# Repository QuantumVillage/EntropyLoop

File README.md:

```
   _   _   _   _   _   _   _  
  / \ / \ / \ / \ / \ / \ / \ 
 ( E | N | T | R | O | P | Y )
  \_/ \_/_\_/_\_/_\_/_\_/ \_/ 
        / \ / \ / \ / \       
       ( L | O | O | P )      
        \_/ \_/ \_/ \_/                                                                                                         
```

**An open source Phase-Diffusion Quantum Random Number Generator**

**2026-04-17 UPDATE** - Now the first AI native QRNG! [/mcp](/mcp) and away!

QV is pleased to be releasing the ‘Entropy Loop’ for world Quantum Day on April 14th 2026: This is a USD $35 open source Quantum Random Number Generator made using off the shelf fiber optics and a raspberry pi pico - in a credit-card sized package!!

Entropy is fast becoming a fundamental resource, especially as AI, simulations, optimizers, cryptography, and computing in general are all changing and accelerating in reach and usefulness. We believe the best way to democratize this technology is to open source a ‘strong minimal viable example’, as we did with quantum sensing, and provide a fully working off the shelf BOM with firmware that passes all major entropy quality tests. This project also serves as an educational/informational demonstration of the benefits of Quantum RNG over regular TRNG and (CS)PRNG technologies.

**Coming Soon** - We want to illustrate a few key use cases for quantum entropy; AI, Simulations, and ART!

Here's what the completed build looks like:

## Randomness from Vacuum Fluctuations

When a laser diode powers up, there are quantum fluctuations that occur that later determine the laser's current phase and polarization during operation. This means that if we pulse a laser diode on, then off long enough to let it totally power down, and then repeat, each pulse has unique and 'quantum random'-ly determined properties. 

We can send these pulses into an optical fiber network, and split the pulse so that ~50% goes straight over to the detector, and the rest gets sent to a delay line - here, we use 5m length of fiber as our photonic delay line. 5m is long enough that with the timing of our pulses (roughly every 24ns, @ 42MHz) the pulse travelling over the delay loop will interact with the next pulse from the laser diode. 

The fact that each of these have different phase and polarization properties, and randomly so, means that their interactions are fundamentally chaotic and random. This is great, for a QRNG - and so this is what we estimate and measure. You can see examples of the pulses below. 

Details for the background physics maybe found in the paper [Ultra-fast quantum randomness generation by accelerated phase diffusion in a pulsed laser diode](https://opg.optica.org/oe/fulltext.cfm?uri=oe-22-2-1645) by Abellán et al.

## Build Instructions

If you would like to jump to our build guide for the Entropy Loop, take a look at [BUILD.md](BUILD.md). 

## System Overview

Here's an overview flowchart of what's going on in this system:

```mermaid
---
title: PD-QRNG Process Flow
---

flowchart TD
    subgraph Fiber Optics
    L[Laser Diode]
    D[Detector]
    end
    subgraph R[<div style="width:30em; height:8em; display:flex; justify-content: flex-start;">Raspberry Pi Pico</div>]
        I[Pi Pico Init]
        subgraph PIO [<div style="width:10em; height:8em; display:flex; justify-content: flex-start;">PIO</div>]
        A[Narrow Pulse Wave]
        end
        subgraph Core 1
        G[Gather Entropy]
        end
        subgraph Core 2
        M[Calculate Min-Entropy]
        S[Generate SHA512 Hashes]
        U[Send Data over UART]
        end
    end
    B[USB Bridge]
    I -->|Initializes Cores| G[Gather Entropy]
    I -->|Loads PIO Program| A
    D -->|ADC read| G
    G -->|Process Data| M
    G -->|Load Raw Samples| S
    S --> U
    M --> U
    U -->|Go Back for More| G
    A  -->|Drives| L
    L e1@==>|pulses sent through fiber network| D
    e1@{ animate: true }
    U ==>|Serial Connection| B
```

### Software Overview

The software is available in C and MicroPython. This guide covers the C code, but there is a commented variant in MicroPython located in [python-scripts/QRNG.py](python-scripts/QRNG.py). The only difference is that MicroPython doesn't have SHA512 available, so we use SHA256 instead. 

There are three parts to this system; the PIO program, the ADC acquisition code, and the min-entropy calculation and hashing code communicating over UART over USB.

The Pi Pico is overclocked to 244.8MHz to synchronize the laser pulse cycle with the propagation delay of light through a 5-meter fiber optic cable.

The timing is based on the speed of light in the fiber, calculated using its refractive index. (For Corning SMF-28 fiber, the refractive index is approximately 1.4682 at 1550 nm and 1.4676 at 1310 nm.) This results in a propagation delay of approximately 24.49 ns over 5 meters at either wavelength.

The PIO pulse cycle consists of six clock cycles: one cycle with the laser on, followed by five cycles with the laser off to allow the laser diode to fully desaturate before the next pulse. Matching this six-cycle period to the fiber propagation delay produces an ideal system clock frequency of approximately 245 MHz.

The Pico is therefore configured to operate at 244.8 MHz, the nearest achievable clock frequency to the calculated optimum. At this frequency, each clock cycle lasts approximately 4.085 ns, producing a laser-on pulse of 4.085 ns followed by a laser-off interval of 20.425 ns. The complete pulse cycle is 24.51 ns, closely matching the fiber's optical propagation delay of 24.49 ns.

This timing is intended to ensure that the laser diode has sufficient time to desaturate between pulses, allowing vacuum fluctuations to contribute to the randomness of the emitted photons while maintaining synchronization with the optical delay line.

The PIO code sets is as follows:

```c
.wrap_target
    set pins, 1 
    set pins, 0 [4]
.wrap
```

The code on core 0 is the ADC acquisition code. It reads the signal that is biased at 1.65V, exactly in the center of the Pico's 3.3V ADC range. The ADC is 12-bit, meaning our readings are centered around the value 2048, with a maximum of 4096. The ADC measurements are collected in window arrays of length 1024 `int` values, and passed through a blocking write to an array owned by core 1. 

Core 1 runs the min-entropy calculation code and manages UART communications. It performs an optimized min-entropy calculation that performs a lagged look-around analysis to generate a histogram of delta difference values for each of the measurements. This normalizes the calculation from being 'peak heavy' from the pulsed nature of the randomness, and attempts to avoid any incidental features from the 500kHz max speed of the Pico's ADC. Given we are using a window of 1024 (2^10) samples, the maximum value for min-entropy is 10. The min-entropy calculation code is as follows:

```c
for(int i = 0; i < BATCH_SIZE; i++) {
    // Mask to ensure we only look at 12 bits
    uint16_t val = batch.samples[i] & 0xFFF;
    
    // --- Update Min/Max (Raw Data) ---
    if (val < min_val) min_val = val;
    if (val > max_val) max_val = val;
    // ---------------------------

    // --- LAGGED DERIVATIVE CALCULATION ---
    // 1. Get the "Old" value from history
    uint16_t old_val = history[hist_head];
    
    // 2. Overwrite history with current value
    history[hist_head] = val;
    
    // 3. Advance the ring buffer head
    hist_head = (hist_head + 1) % LAG_DEPTH;

    // 4. Calculate Delta against the OLD value
    // We add 2048 to center the result.
    uint16_t delta = (val - old_val + 2048) & 0xFFF;
    // -------------------------------------

    // Update Histogram using DELTA
    if(counts[delta] < 65535) counts[delta]++; 
    if(counts[delta] > max_count) {
        max_count = counts[delta];
    }
}

// Calculate Min-Entropy
float min_entropy = 10.0f - log2f((float)max_count);
// scale for 8-bit min-entropy - for 10.0f it's 8/10.0
min_entropy *= (8.0/10.0);

// Calculate Range
uint16_t dynamic_range = max_val - min_val;
```

## Hardware

### Bill of Materials

**Optics:**

* 2x fiber splitters - 1x2 or 2x2
* 1x Delay line (5 meters)
* Optical connectors

For our assembly, we use SC/APC fiber connectors. These are square with angled ends that minimize reflections at any interfaces. 

**Electronics:**

* 1x Raspberry Pi Pico (or Pico 2)
* 1x Prototype Board
* 1x pair of fiber optic transceivers
* 1x 10nF ceramic capacitor
* 2x 10k Ohm resistors (through hole)
* 1x prototyping board
* Assorted connection wires

Many optical transcievers transmit/receive on 1310/1550nm or tx/rx at 1550/1310nm. (1310nm is in O-band and 1550nm is in C-band in conventional fiber optic parlance). 

### Prototype Board Assembly

The following summarises the pin assignments for the Pico:

* `GPIO0` is used as the laser driver. A PIO program is run to offload this from the CPI.
* `ADC0` is used to read the data from the receiver, running on core 0
* The USB port is used to analyse and generate the final randomness and min-entropy outputs, and is controlled from core 1. 

### Optical Assembly

This is a sketch overview of the RPi pico driver, laser/PD and splitter setup. The Delay Loop used below is 5m in length.

This is what the system looks like in hardware:

### Circuit Details

`GPIO0` and `ADC0` are used on the RPi Pico. Here are more details:

* The `3V3` and `GND` pins (3rd and 5th on RHS) are used to power the two fiber modules.
* Both an A and a B module are used - one transmits at 1310 and receives at 1510, the other at 1510 and receives at 1310.
* Pin 8 on the A module (`TX` positive pin) is used to drive the laser.
* Pin 2 on the B module (`RX` positive pin) is used to receive.
* Between this `RX` pin and the `ADC0` pin, there is a small circuit that normalizes the voltage from being centered around 0V to being centered around 1.65V. This circuit is comprised of:
    * 2x 10k Ohm resistors are used. On is connected to `3V3` and the other to `GND` they form a voltage divider the middle of which is tied to `ADC0`.
    * 1x 10nF ceramic capacitor is used - this goes from `RX` to `ADC0` that has the voltage lift from the divider. 

The circuit schematic for the output level shifter looks like this: 

## Bill of Materials

The full BOM is as follows:

1. 1x PAIR Fiber Transcievers - e.g. https://www.aliexpress.com/item/1005010400110455.html
1. 1x 5m fiber patch cable - e.g. https://www.aliexpress.com/item/1005008760544957.html
1. 2x 1x2 50/50 fiber splitters - e.g. https://www.aliexpress.com/item/1005006647801937.html 
1. 3x SC/APC Fiber Couplers - e.g. https://www.aliexpress.com/item/1005008790973325.html
1. 1x Raspberry Pi Pico
1. 1x Prototyping board
1. 2x 10k Ohm Resistors
1. 1x 10nF ceramic capacitor

### Note on Fiber Choices

For our build, we use SC/APC fiber connector parts - these are usually green in colour. SC Connectors are very easy to use and reconfigure, hence they were chosen. Blue SC connectors are UPC, meaning they have flat ends which can cause reflections of signal. SC/APC connectors have an 8 degree angle cut on the end to minimize reflections, which is ideal for our purposes. Yellow fiber cabling is usually patch fiber, which is what we want to use. We use multimode 9/125 fiber in this build - that is 125um diameter with a 9um core. 

The transcievers we use are usually multimode - that is they have one side that transmits on 1310nm and receives on 1510nm frequencies, and the other side receives on 1310nm and transmits on 1510nm light frequencies. We use 1310nm for Tx/Rx, but the choice of which frequency to use is inconsequential.

## Full Build

### Transiever Pinout

The pinout for each transceiver unit is as follows. Pin 1 is the left-most pin when looking down on the top of the device with the fiber pointing away from you. The pinout is as follows:

We will just use the `RD+` and `TD+` pins for Rx/Tx respectively. Note that you have to supply +3.3V to EITHER the `VCCR` on the Rx side and `VCCT` on the Tx side, as they have separate power supplies.

### Build Overview

If you are using the PCB design, you should end up with something that resembles these examples (credit-card for size):

The Pi Pico uses `ADC0` for Rx and `GPIO0` for Tx - with the 3.3V supply and GND pins powering the units. The overall wiring looks like this from below:

Here is the top view - you can see how the voltage divider and ceramic capacitor:

The capacitor is tied to one side on pin 2 of the receive module, and the other side is tied to the joint between the two resistors in the voltage divider. The push pull of the Rx signal is thereby inverted over the capacitor and shifted to 1.65V, which is the precise middle of the 3.3V `ADC0` range. 

### Fiber Build

The fiber is built exactly as photographed above. The setup is symmetrical, so there is no specified in/out or tx/rx port. The two free ports go to either module.

Remember, the fiber network is essentially an amplifier for the quantum vacuum fluctuations in the laser diode startup.

## Results 

The following show some measurement results off a six metre fiber delay loop in a MZI configuration, with a 38MHz base pulse step with 4 sleep steps following. 

This is the base pulse from the PIO program on `GPIO0`:

Here is the base pulse sent over a 1.5m loop of fiber - 

And here is the full output from the `RX` pin sent to the ADC over the interferometry network:

Here are two zoomed in portions to help show the randomness of the system:

<!-- 
 -->

This is a much zoomed in signal from the receiver:

## But How do we Know It's Quantum?

Suppose we take our transciever setup, and run the Pico as normal. Then let's hook it up to the two splitters. If we just connect one of the fibers between the two, we get the following output trace:

However, if we add both fibers, we get the following trace:

The fact that these are so similar is encouraging, as it means that the two signals are either matching, cancelling out, or adding some more noise from the few extra lengths of fiber.

The following is the output when you add the delay line back between one of the connections between the splitters - the dramatic change in the signal despite the same oscilloscope settings means that we are surely seeing some kind of quantum interference resulting from the vacuum fluctuations in the laser diode startup:

We can look at some zoomed-in versions to see the difference. Here is the signal with one connection between the splitters:

Here is the signal zoomed-in with two arms connected - we can see that the signal is in part amplified and in others slightly variable:

With the delay line included, we can see the randomness in the signal from the interference of the non-matching laser pulses:

### Comparison of PIO Signal to Output

Here is the base signal with the base pulse in purple:

Here is the baseline random signal from the interference with the baseline signal in purple again:

Note that there is a 'peak-y-ness' in the signal that correlates with the baseline somewhat. This is why we use jittered readings to avoid falling into traps around that potential correlation. 

## Entropy Tests

### Running `ent`

On a file with 256 million raw bytes converted from the input, the following result was obtained from running the `ent` entropy test suite, a standard tool in Linux:

```bash
user@qrng:~$ ls -l qrng_dump.bin 
-rw-rw-r-- 1 user user 256000000 Feb  4 14:28 qrng_dump.bin
user@qrng:~$ ent -b ./qrng_dump.bin 
Entropy = 1.000000 bits per bit.

Optimum compression would reduce the size
of this 2048000000 bit file by 0 percent.

Chi square distribution for 2048000000 samples is 0.15, and randomly
would exceed this value 69.96 percent of the times.

Arithmetic mean value of data bits is 0.5000 (0.5 = random).
Monte Carlo value for Pi is 3.141611487 (error 0.00 percent).
Serial correlation coefficient is 0.000025 (totally uncorrelated = 0.0).
user@qrng:~$ 
```

Things of note - Entropy of "around 1 bit per bit" is ideal. Chi-squared values need to be between 0.05 and 0.95, so 0.65 is pretty reasonable. Serial correlation less than 0.00005 is usually considered pretty good, too. 

Calculating >2 digits of pi with randomness is pretty hard - this is for the same reason that `22/7` is such an unreasonably good approximation of pi; the continued fraction of pi has a very large term (292) in it's fourth coefficient (`[3;7,15,1,292...]`). This means that getting `3.1416` vs `3.1415...` (0.0001 off) on a reasonably small dataset is encouraging. 

On this test suite, the randomness is performing pretty well, it seems!

### NIST STS

This is a gold-standard test suite from the NIST standardization people. Here is the output of the full run, showing what parameters were used with `sts-2.1.2` version:

```
user@qrng:~/nist/sts-2.1.2/sts-2.1.2$ ./assess 1000000
           G E N E R A T O R    S E L E C T I O N 
           ______________________________________

    [0] Input File                 [1] Linear Congruential
    [2] Quadratic Congruential I   [3] Quadratic Congruential II
    [4] Cubic Congruential         [5] XOR
    [6] Modular Exponentiation     [7] Blum-Blum-Shub
    [8] Micali-Schnorr             [9] G Using SHA-1

   Enter Choice: 0

                User Prescribed Input File: data.bin

                S T A T I S T I C A L   T E S T S
                _________________________________

    [01] Frequency                       [02] Block Frequency
    [03] Cumulative Sums                 [04] Runs
    [05] Longest Run of Ones             [06] Rank
    [07] Discrete Fourier Transform      [08] Nonperiodic Template Matchings
    [09] Overlapping Template Matchings  [10] Universal Statistical
    [11] Approximate Entropy             [12] Random Excursions
    [13] Random Excursions Variant       [14] Serial
    [15] Linear Complexity

         INSTRUCTIONS
            Enter 0 if you DO NOT want to apply all of the
            statistical tests to each sequence and 1 if you DO.

   Enter Choice: 1

        P a r a m e t e r   A d j u s t m e n t s
        -----------------------------------------
    [1] Block Frequency Test - block length(M):         128
    [2] NonOverlapping Template Test - block length(m): 9
    [3] Overlapping Template Test - block length(m):    9
    [4] Approximate Entropy Test - block length(m):     10
    [5] Serial Test - block length(m):                  16
    [6] Linear Complexity Test - block length(M):       500

   Select Test (0 to continue): 0

   How many bitstreams? 200

   Input File Format:
    [0] ASCII - A sequence of ASCII 0's and 1's
    [1] Binary - Each byte in data file contains 8 bits of data

   Select input mode:  1

     Statistical Testing In Progress.........

     Statistical Testing Complete!!!!!!!!!!!!

```

The results are in [`20260209-finalAnalysisReport-nist-sts-2.1.2-1000000-200.txt`](20260209-finalAnalysisReport-nist-sts-2.1.2-1000000-200.txt). Some notes:

* `0.474986 200/200` for Approximate Entropy is a perfect score
* The Universal test (compressibility) has a very fine score at `0.930026 197/200`
* Generally, results are >= 193/200.
* `Frequency: 197/200` is a strong result.
* `Runs: 200/200` (The "Coin Flip" consistency is perfect)
* `FFT: 198/200` (No periodic sine-wave noise detected)
* `Linear Complexity: 199/200` (Mathematically complex)

This is a pretty reliable showing in the NIST STS tests!

## Sample Serial Output

Here is some example output from the UART connection. `H_min` is the output of the min-entropy calculation. When scaled to 8 bits, ~6-6.4 is considered generally good. `R` is the range, and `Data` precedes two lines of `SHA512` hashes that are the condensed versions of the input entropy pools:

```bash
H_min: 6.4000 | R: 1918 | Data: 
443873b9af95c4671de53ede1f37af2f78408a903300402543a34a06020aa305c09b0bcea871f904c372c40d79e6035c89a2711f412869b5a05652051dbfac67
d530286e8019a42a8ae438069d4621a9911630763abc80a3125b4f1f0452eb92756abd615073a2da890c3ca5808bbc866dcea88fa74e5539537c7104e0722f3c
H_min: 6.1425 | R: 1950 | Data: 
f0b5757e5fe9591ffc66a6ced7bf63c96838fa9df56f366fce90f07ed2ef06784f5ba94b515a9a42c2b13a4b6f5175f0dfe105297ab661c1208994a6aca6be4b
33c6c05e40a60159f14c41c28ee8776daf82613df46fb542fcb2eb2bf6d3aae50eab5d88226b226b91baa0837d19b883117379b2ef41808076bb43b0daa5941c
H_min: 6.4000 | R: 2011 | Data: 
2e07d14ec204998db14837cad48da2c273f100264779920bbebb92e8208ab1484c863162b24baa2da8da6b7945f3a7a6f85a936c37de6345f181d7fdb6b4c3a1
26ee2365af42f27a8d64097024393df73e5ea65b2386062645fe1346006324c6d678e08f1b1a32deeb540cefb8a982079c72bc777162d5188ecbac2e398a5b44
H_min: 6.4000 | R: 1986 | Data: 
337e48c7376a80b0e43b932615866200de07d32e855f63956073ab6aa83fb87f9524ecd4503aa5a3633824c69cddad1734a44bc7f0685c7dccec9892455fc66e
4bf61aa3b0e67d1cac27f887e0d6b1aaf26181b14048d6834875f49160590e7c6dd7f5b84c7ef79b4e51ebe840208673d65dd83c78856fea4d1e06def112e8ab
H_min: 5.7541 | R: 1828 | Data: 
cc973979268c01a256b1f7c1f226f3741a06034923c8cb8b452da0b09ffa05b256df2bde82461249158728a9bb74b89143cb34be45561cf723f64201bb5d9547
286caf718f46534027ddc94c3432383939fdc79027dbcb5a487c42e33cb09bf8876675718b4c37cc42f7378736ace144857e9b767dac2c30c2549cc81d4ee1b4
H_min: 6.4000 | R: 1839 | Data: 
6aa747abc770854975d74c763407b2fd151ebbc53ae27084d2d55084dcf394903a6c9841217591ff92a13f3f10bfd8a3b82c2b0ce2ef096590024fd1c93d56fd
62b8e07aaeb52128169e41d9c77f14a0c66dac61ef11325dba470b5d6005668d14b43e5f44c5a4f657f5f51c45488909abd7a0001b8abc3f05fceae6b3832994
H_min: 6.1425 | R: 2034 | Data: 
853e63609444bd463b8acc818e39d7ad5fba318f25a71634dd97edefaa8078b462a20ffce2dfc9081d327e3bda971b9eb139674d1370379de49f712a601b0178
9fffab38b70490f84225ad8d432040bfa0007604d99cc4d89062b60788177c3dbcf663a890ee3b31fb18d553476f54c8de89823c984ea6653326192da4cfd811
H_min: 5.9320 | R: 1824 | Data: 
15d2f45addaecf805045659a7a7764ef39c73e8e403ee7e37e8bb92ab8482846da3ed463b42cdfaec0f1c1c84dd400c69c32312f63d3d16044a192cc7ef23752
8d1ec1bb5ae9b8588219cf4f12aad1076d1c6872df68ea6e431a4a24e1f4c5bf793d33a27da6aa7d012d2c338c6333ad42dd180820311d8c6ef9d81230558f09
H_min: 6.4000 | R: 2021 | Data: 
fa5ad3478acb174873311625d4d543d1edf3c6c6527002d0a374e4af4fe89c67988e25f0669d5a84ef9f2f0f285fa8ef56c92ed165c887603dddd20afca39cba
1028a9831090576b02f8fdb6ef68872d2b4e0f4b1823a0cba7e9f82718e798b06928d22fb90b1668b8a0e0b8a9cfe79cd492e64aee1fd4e48294420a93d37da4
H_min: 6.4000 | R: 1936 | Data: 
ed30f574e2b04bcb051d67047dde8a0842dd2fda9098914daa70570892391264a113f031553a4eacde3053701320495807773bf609f122554db7c898d7e5c6b3
d029184e8afb121cebfea3a4c23f1165839b05e7b171aff8fbbe77be89a0a07863498280a01d85e3eaa854719aa9a111ded448e6d89e154909b8b328a4f8850b
H_min: 6.4000 | R: 1940 | Data: 
2ba336de86fc9a3c979d21a3adb4bd92e0ca8911ee1f676723bf9325a9f496e5bc951808f4c43db71a6292a3bccffb4783992e8d1c775b5b7a5650b4d42fb3d7
736276f7c2264c1bad9cadab5a55cb96eb401da8913b35eeccbab3a4fcd762c0a81f7c00122ec527a8f67e59c565ced42ae1a8ac2a3d37f3153fa966e4f99a61
H_min: 6.4000 | R: 1972 | Data: 
103f16490da66756b70ed2787f4012fd5ba894a9067591155c718e8669afb0e979d83f3ec5d531bf9bdecadfd3897eafca9323384daf4a46f4c190820ddfdc82
8ea2d7bd19b792baa3458a0831d71078efcf4232c2d2933966c761e8d36ce8cadcd4cdfee128014802be5315b7761cf34b05069f30be1ab9c4886a65325e7083
H_min: 6.1425 | R: 1956 | Data: 
498b9d036b77fa9294dea3043eb20998103514f0c8c0bfa7c79cc1ee6bee675da76e10db003e2d8d656bafc5954bc816451b48df74ba32cadd5b3161c60cd215
8956642194ae2d9ceaa2e97f69fea594d1ea65ea16b6121be89f465594add880c5d4afc87643768840da0e54124cb81b4bb5abd286c55ef8176980bc72224412
H_min: 6.1425 | R: 1925 | Data: 
07085ec0352fb6853b2a79e40ebb86f2a13166b173c6c21c2f8da378dd93bd50d3d5b95f3514ccfd1517593f589a2fcd1b470937eaaf9a692dff998121a6456a
491454d92d2dcb301fe41e5745cf9fe742fe1e5b04bce5ad51d0d7c6f4eaf318c6ce491ffb21543f7167fc488a2e0523e6a69a21b0c42eca6275b880ce7170a6
H_min: 6.4000 | R: 1954 | Data: 
f0224d88000652e386231a7e596df556c80bb06b99a23a6644ba36cfa9689c4788fcbe78fd053da6b8580fc26c381dd2c3380f86a2839ecde010fbc1ce8810a5
cf9b05b8deddf0c9909b8caf2f479a612f97e9e6e00c2bdc3195e37dc35da1268cd67c73795485f954209cd02709e398533f4efcf8ea30ed7d8ae34f037312d6
H_min: 6.4000 | R: 1855 | Data: 
75fa43d80123b479414758c09433c51612fa482737b2a10c9eee5a64af7895b71b37e265aeb47a38fa77667c40eef1aa162d997e1f256e30ff26280764c04058
567d2cf0192a0301d4f5782d4b8d0cea3e31f43d5b484bd7a4c9850927fadce7082137b5b1346d1c4328f5d6d2528a0421703831c497564db39ba6056ab8fa65
```

## Conclusion

This project has showed the potential for low cost, high performance, field-ready designs for PD-QRNG.

## Acknowledgements 

We are grateful to Eric Case and Dr. Evan Anderson for their help and contributions to validation and testing the design, as well as the Quantum Village community's continued enthusiasm for lo-fi DIY 'bits box' Quantum!

This project was supported by a grant from the Mozilla Foundation to whom we are very grateful.

## References

The primary reference is Abellán et al. "Ultrafast Quantum Randomness Generation by Accelerated Phase Diffusion in a pulsed laser diode", 2014, link: https://opg.optica.org/oe/fulltext.cfm?uri=oe-22-2-1645.

A secondary reference, "Quantum Entropy Source on an InP Photonic Integrated Circuit for Random Number Generation" by Abellán et al. is good resource for understanding vacuum fluctuations, and how they can be utilized; Link: https://opg.optica.org/optica/fulltext.cfm?uri=optica-3-9-989.

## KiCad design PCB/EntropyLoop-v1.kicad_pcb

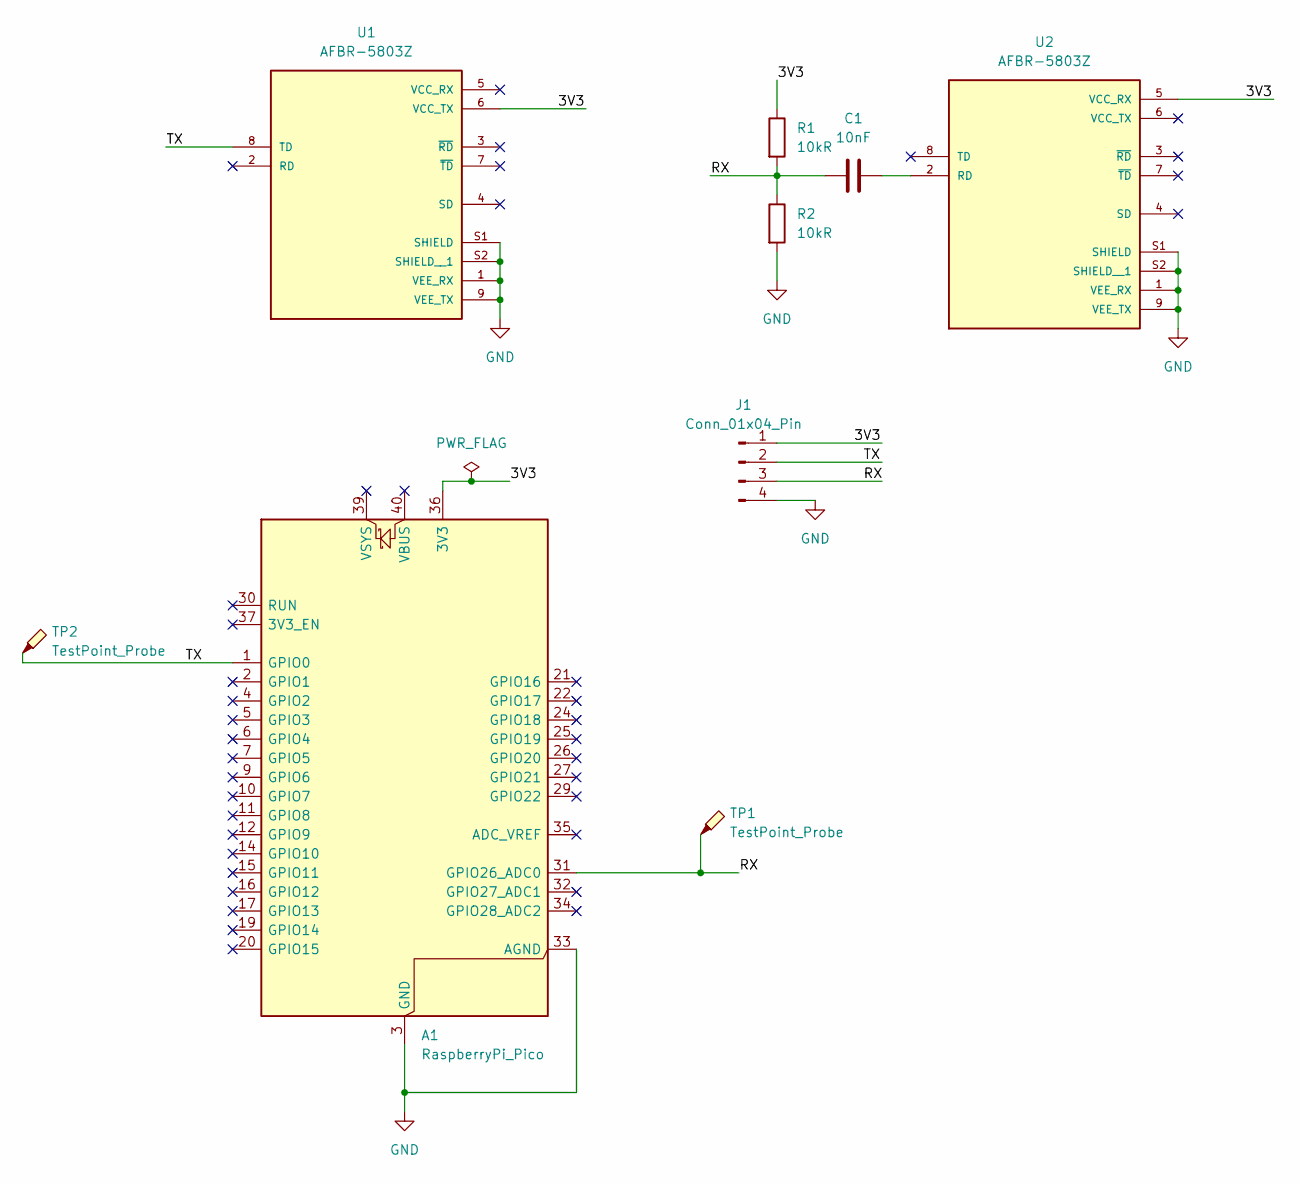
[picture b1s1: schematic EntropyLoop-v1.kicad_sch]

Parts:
A1: RaspberryPi_Pico; RaspberryPi_Pico_Common_Unspecified
C1: 10nF; C_Disc_D4.7mm_W2.5mm_P5.00mm
J1: Conn_01x04_Pin; PinHeader_1x04_P2.54mm_Vertical
R1, R2: 10kR; R_Axial_DIN0207_L6.3mm_D2.5mm_P7.62mm_Horizontal
TP1, TP2: TestPoint_Probe; TestPoint_Loop_D2.54mm_Drill1.5mm_Beaded
U1, U2: AFBR-5803Z; XCVR_AFBR-5803Z; PARTREV March 24, 2017

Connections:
/3V3: A1.36 (3V3), J1.1, R1.1, U1.6 (VCC_TX), U2.5 (VCC_RX)
/RX: A1.31 (GPIO26_ADC0), C1.1, J1.3, R1.2, R2.1, TP1.1
/TX: A1.1 (GPIO0), J1.2, TP2.1, U1.8 (TD)
GND: A1.3 (GND), A1.8 (GND), A1.13 (GND), A1.18 (GND), A1.23 (GND), A1.28 (GND), A1.33 (AGND), A1.38 (GND), J1.4, R2.2, U1.1 (VEE_RX), U1.9 (VEE_TX), U1.S1 (SHIELD), U1.S2 (SHIELD__1), U2.1 (VEE_RX), U2.9 (VEE_TX), U2.S1 (SHIELD), U2.S2 (SHIELD__1)
unnamed: C1.2, U2.2 (RD)

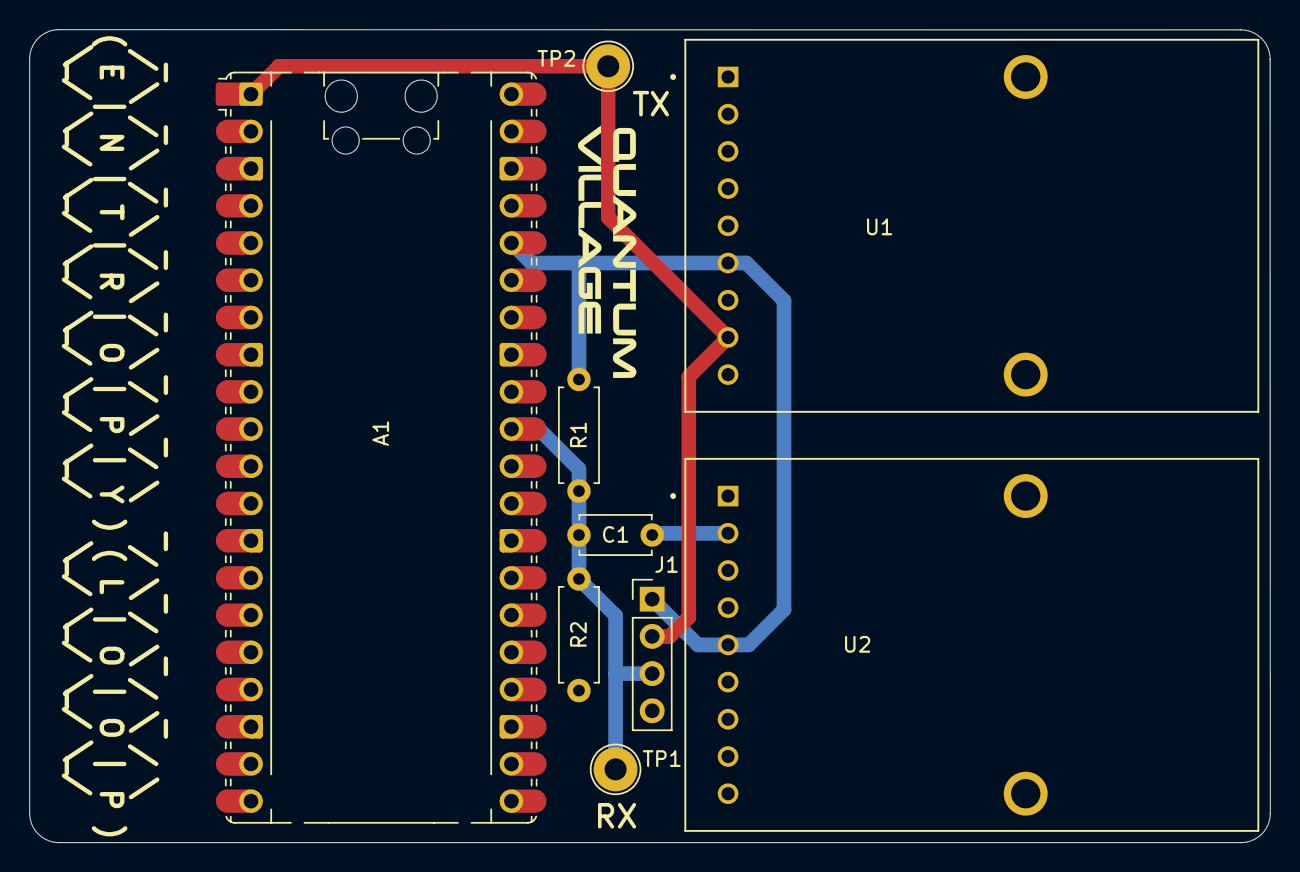
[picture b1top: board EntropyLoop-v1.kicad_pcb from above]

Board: 2 copper layers, 84.7 x 55.5 mm, 9 parts (0 on the bottom side), 5 nets.

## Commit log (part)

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2026-03-23 first pcb design up
2026-03-23 added schematic plots
2026-03-29 updates for updated pico-sdk
2026-04-03 Update README with Entropy Loop project details
    Added details about the 'Entropy Loop' Quantum Random Number Generator and its significance in the context of AI and cryptography.
2026-04-13 removed read jitter to make the entropy measurement more sensitive
2026-04-13 added build guide
2026-04-13 removed measurement jitter from python variant
2026-04-13 Add CITATION.cff for software citation information
2026-04-13 updated imagery
2026-04-13 updated copy
2026-04-13 Create LICENSE
2026-04-13 fixed the readme
2026-04-13 added note for applications
2026-04-14 added note for acknowledgements
2026-04-17 creating an MCP server for Entropy Loop
2026-04-17 Update README with AI native QRNG announcement
    Added update about the first AI native QRNG and details about the Entropy Loop release.
2026-04-17 updated comment
2026-05-31 Add dual-path README - balanced differential detection extension of EntropyLoop
2026-05-31 Add Build 3.1a firmware - AD7606 drift-resistant DC blocker Von Neumann 250MHz
2026-05-31 Add Build 3.1a CMakeLists.txt
2026-05-31 Add Build 2.1 functional baseline binary (154K) - PIO I2C ADS1115 dual channel confirmed working
2026-05-31 Add Build 3 Grafana dashboard - H_min VN bias RCT APT health panels
2026-05-31 Add Build 3.2 production binary - busy-race fix 6.2-6.9 bits/byte sustained
2026-05-31 Add Build 3 Grafana dashboard - H_min VN bias RCT APT NIST health panels
2026-05-31 Correct sustained performance range for AD7606 3.2
2026-06-30 adding some early examples
